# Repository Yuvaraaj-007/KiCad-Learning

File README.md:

# KiCad Learning Projects

This repository contains my PCB design practice projects created while learning KiCad.

## Projects

### 1. LED PCB Design
- My first PCB design project
- Designed a simple LED circuit with a current-limiting resistor
- Learned schematic creation, PCB routing, and DRC verification

### 2. 555 Timer LED Blinking Circuit
- Designed an astable multivibrator using the 555 Timer IC
- Created an LED blinking circuit using resistor-capacitor timing components
- Learned the working of the 555 Timer in astable mode
- Improved PCB layout and routing skills

### 3. Push Button LED Circuit
- Designed a circuit to control an LED using a push button switch
- Learned switch connections and basic input-output circuits
- Practiced schematic design and PCB layout creation

### 4. Transistor LED Circuit
- Designed an LED switching circuit using a transistor
- Learned the basics of transistor operation and switching applications
- Improved understanding of electronic components and PCB design workflow

### 5. Traffic light controller
- PCB schematic design
- PCB layout and routing
- Design Rule Check (DRC)
- KiCad workflow
- Electronic circuit design
- 555 Timer applications
- Switch and transistor circuits
- Traffic light controller design
- Complex PCB routing and component placement

## Skills I Am Learning

- PCB schematic design
- PCB layout and routing
- Design Rule Check (DRC)
- KiCad workflow
- Electronic circuit design
- 555 Timer applications
- Switch and transistor circuits

## Goal

To improve my PCB design skills, strengthen my electronics knowledge, and build real-world embedded and PCB projects step by step.

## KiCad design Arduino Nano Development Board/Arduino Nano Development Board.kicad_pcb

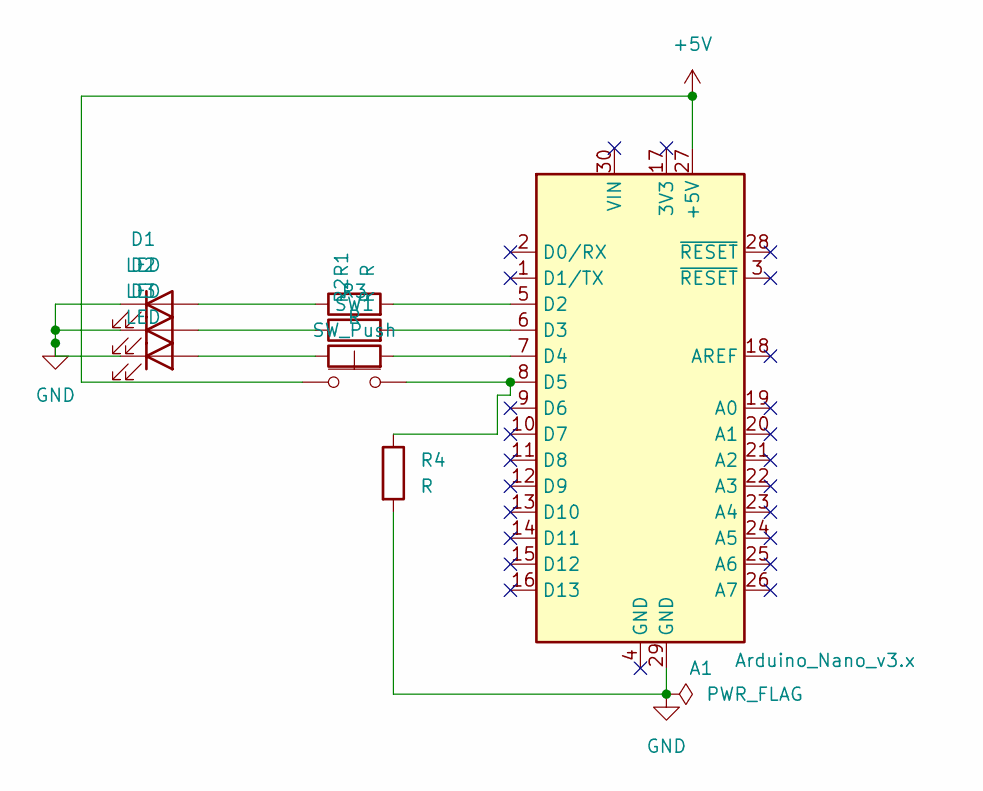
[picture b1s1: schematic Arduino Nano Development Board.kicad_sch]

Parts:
A1: Arduino_Nano_v3.x; Arduino_Nano
D1, D2, D3: LED; LED_D5.0mm
R1, R2, R3, R4: R; R_Axial_DIN0207_L6.3mm_D2.5mm_P7.62mm_Horizontal
SW1: SW_Push; SW_PUSH_6mm

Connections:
+5V: A1.27 (+5V), SW1.1
GND: A1.29 (GND), D1.1 (K), D2.1 (K), D3.1 (K), R4.2
unnamed: A1.5 (D2), R1.2
unnamed: A1.6 (D3), R2.2
unnamed: A1.7 (D4), R3.2
unnamed: A1.8 (D5), R4.1, SW1.2
unnamed: D1.2 (A), R1.1
unnamed: D2.2 (A), R2.1
unnamed: D3.2 (A), R3.1

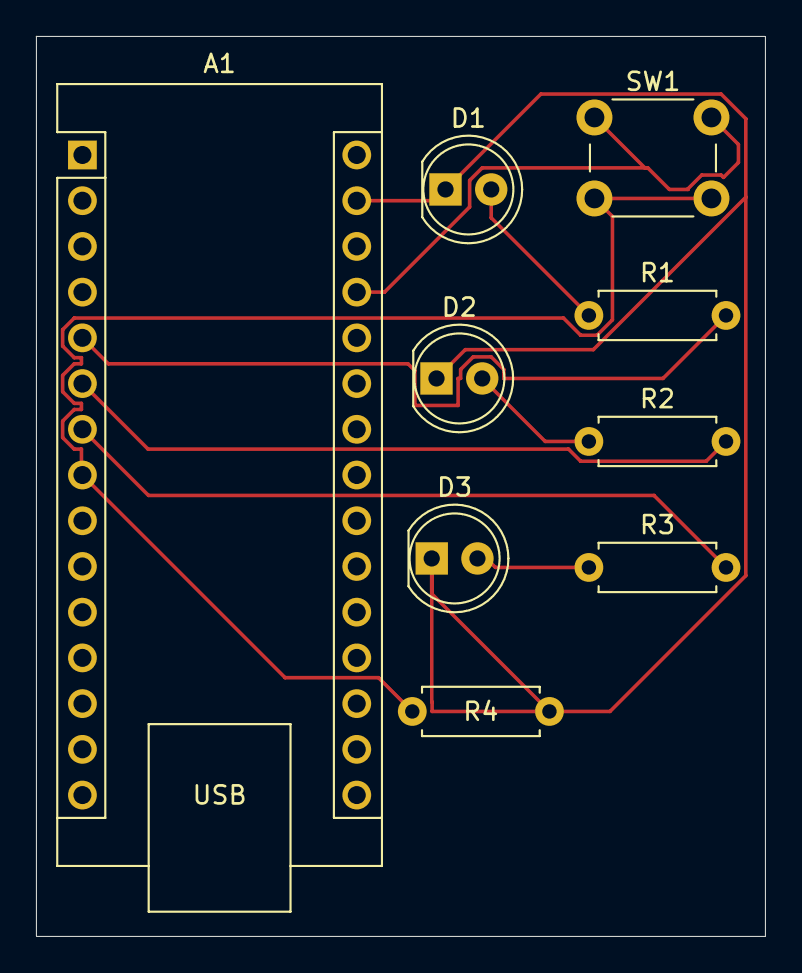
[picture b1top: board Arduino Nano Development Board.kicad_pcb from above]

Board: 2 copper layers, 40.5 x 50.0 mm, 9 parts (0 on the bottom side), 9 nets.

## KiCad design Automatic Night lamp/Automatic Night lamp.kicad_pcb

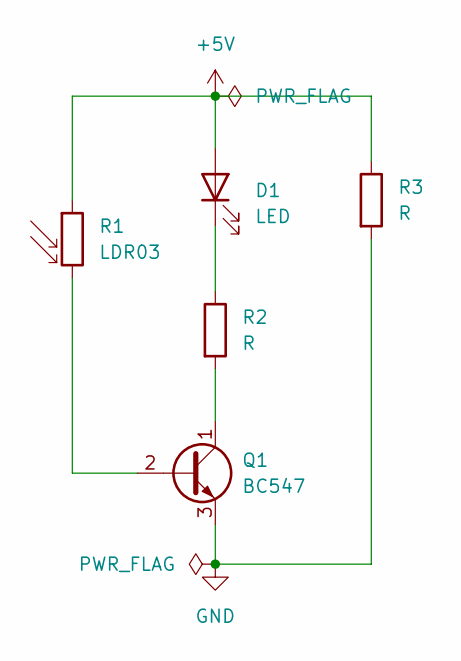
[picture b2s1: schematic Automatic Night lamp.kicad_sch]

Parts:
D1: LED; LED_D5.0mm
Q1: BC547; TO-92_Inline
R1: LDR03; R_LDR_10x8.5mm_P7.6mm_Vertical
R2: R; R_Axial_DIN0207_L6.3mm_D2.5mm_P7.62mm_Horizontal
R3: R; R_Axial_DIN0204_L3.6mm_D1.6mm_P7.62mm_Horizontal

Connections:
+5V: D1.2 (A), R1.1, R3.1
GND: Q1.3 (E), R3.2
unnamed: D1.1 (K), R2.1
unnamed: Q1.2 (B), R1.2
unnamed: Q1.1 (C), R2.2

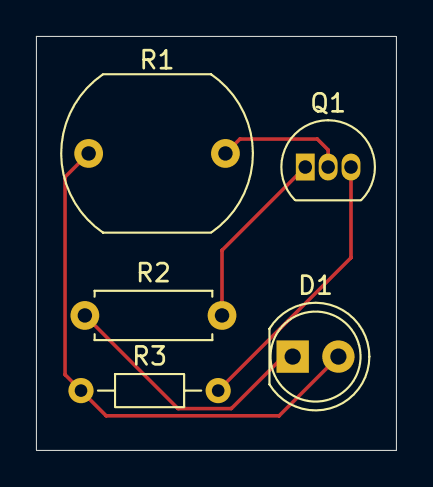
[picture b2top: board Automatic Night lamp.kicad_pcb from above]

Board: 2 copper layers, 20.0 x 23.0 mm, 5 parts (0 on the bottom side), 5 nets.

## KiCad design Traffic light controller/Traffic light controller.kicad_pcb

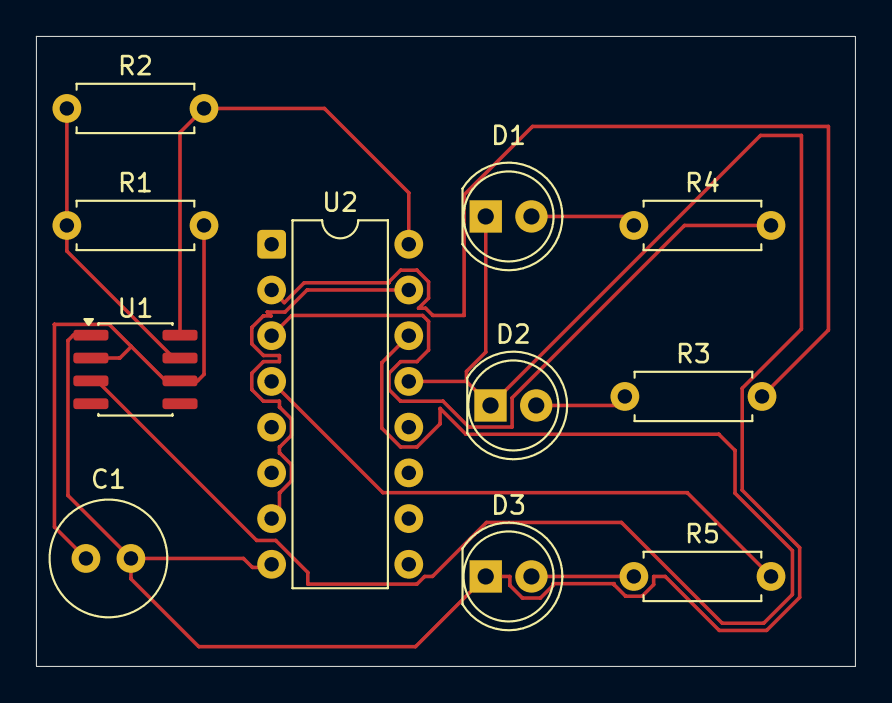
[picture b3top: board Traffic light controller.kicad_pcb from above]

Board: 2 copper layers, 45.5 x 35.0 mm, 11 parts (0 on the bottom side), 11 nets.

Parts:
C1: 10uF; C_Radial_D6.3mm_H5.0mm_P2.50mm
D1: Red; LED_D5.0mm
D2: Yellow; LED_D5.0mm
D3: Green; LED_D5.0mm
R1: 100K; R_Axial_DIN0207_L6.3mm_D2.5mm_P7.62mm_Horizontal
R2: 10K; R_Axial_DIN0207_L6.3mm_D2.5mm_P7.62mm_Horizontal
R3, R4, R5: 330; R_Axial_DIN0207_L6.3mm_D2.5mm_P7.62mm_Horizontal
U1: NE555D; SOIC-8_3.9x4.9mm_P1.27mm
U2: 4017; DIP-16_W7.62mm

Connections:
+5V: R2.2, U1.8 (VCC), U2.16 (VDD)
GND: C1.2, D1.1 (K), D2.1 (K), D3.1 (K_1), U1.1 (GND), U2.8 (VSS), U2.13 (CKEN)
unnamed: D1.2 (A), R4.1
unnamed: D2.2 (A), R3.1
unnamed: R1.1, R2.1, U1.7 (DISCH)
unnamed: U1.3 (OUT), U2.14 (CLK)
unnamed: C1.1, R1.2, U1.2 (TRIG), U1.6 (THRES)
unnamed: R4.2, U2.3 (Q0)
unnamed: R3.2, U2.2 (Q1)
unnamed: R5.2, U2.4 (Q2)
unnamed: U2.7 (Q3), U2.15 (Reset)

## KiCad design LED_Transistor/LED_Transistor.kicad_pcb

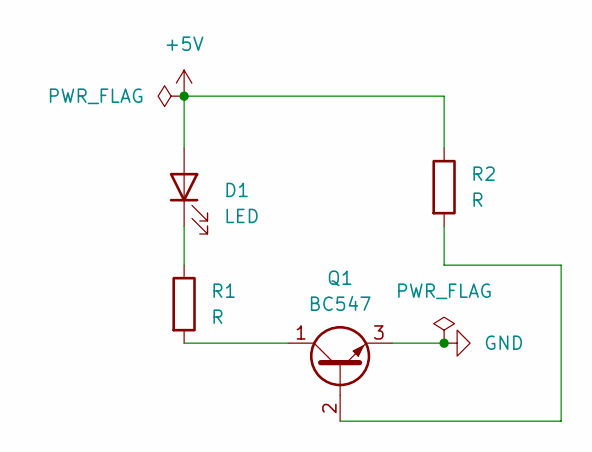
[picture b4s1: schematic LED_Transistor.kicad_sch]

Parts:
D1: LED; LED_D5.0mm
Q1: BC547; TO-92_Inline
R1, R2: R; R_Axial_DIN0207_L6.3mm_D2.5mm_P7.62mm_Horizontal

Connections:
+5V: D1.2 (A), R2.1
GND: Q1.3 (E)
unnamed: D1.1 (K), R1.1
unnamed: Q1.2 (B), R2.2
unnamed: Q1.1 (C), R1.2

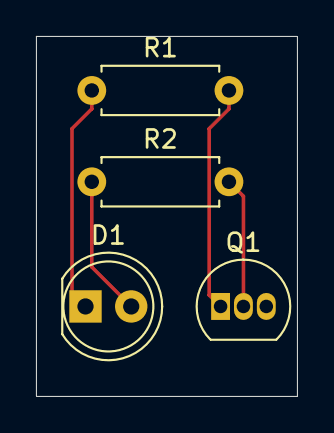
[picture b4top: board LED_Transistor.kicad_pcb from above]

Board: 2 copper layers, 14.5 x 20.0 mm, 4 parts (0 on the bottom side), 4 nets.

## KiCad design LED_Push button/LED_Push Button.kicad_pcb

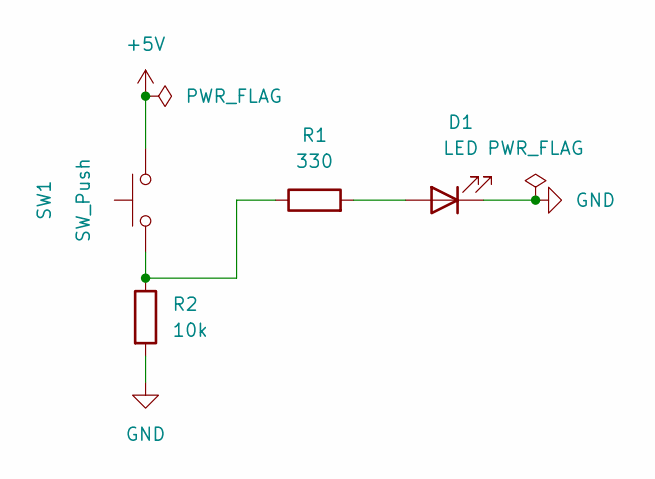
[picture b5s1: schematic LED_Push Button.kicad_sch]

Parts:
D1: LED; LED_D5.0mm
R1: 330; R_Axial_DIN0207_L6.3mm_D2.5mm_P7.62mm_Horizontal
R2: 10k; R_Axial_DIN0207_L6.3mm_D2.5mm_P7.62mm_Horizontal
SW1: SW_Push; SW_PUSH_6mm

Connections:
+5V: SW1.2
GND: D1.1 (K), R2.2
unnamed: D1.2 (A), R1.2
unnamed: R1.1, R2.1, SW1.1

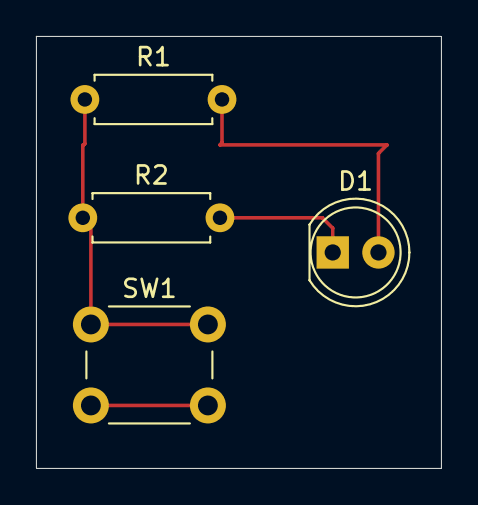
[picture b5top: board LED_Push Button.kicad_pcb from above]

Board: 2 copper layers, 22.5 x 24.0 mm, 4 parts (0 on the bottom side), 3 nets.

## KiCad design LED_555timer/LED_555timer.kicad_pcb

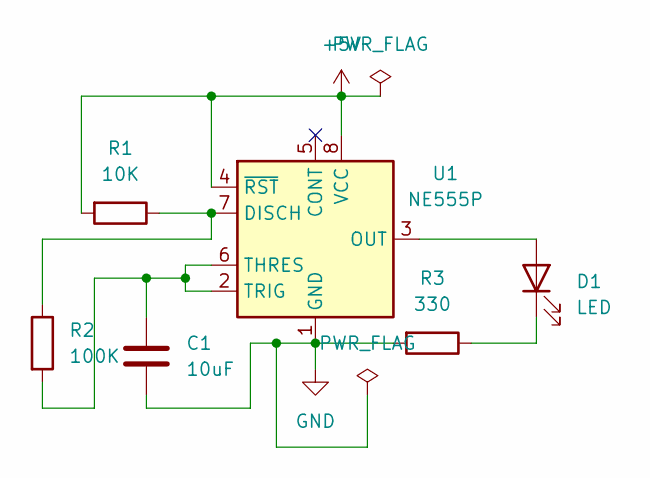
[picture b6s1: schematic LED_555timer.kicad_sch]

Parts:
C1: 10uF; C_Disc_D5.0mm_W2.5mm_P5.00mm
D1: LED; LED_D5.0mm
R1: 10K; R_Axial_DIN0207_L6.3mm_D2.5mm_P7.62mm_Horizontal
R2: 100K; R_Axial_DIN0207_L6.3mm_D2.5mm_P7.62mm_Horizontal
R3: 330; R_Axial_DIN0207_L6.3mm_D2.5mm_P7.62mm_Horizontal
U1: NE555P; DIP-8_W7.62mm

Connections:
+5V: R1.2, U1.4 (~RST), U1.8 (VCC)
GND: C1.2, R3.2, U1.1 (GND)
unnamed: D1.2 (A), U1.3 (OUT)
unnamed: D1.1 (K), R3.1
unnamed: R1.1, R2.1, U1.7 (DISCH)
unnamed: C1.1, R2.2, U1.2 (TRIG), U1.6 (THRES)

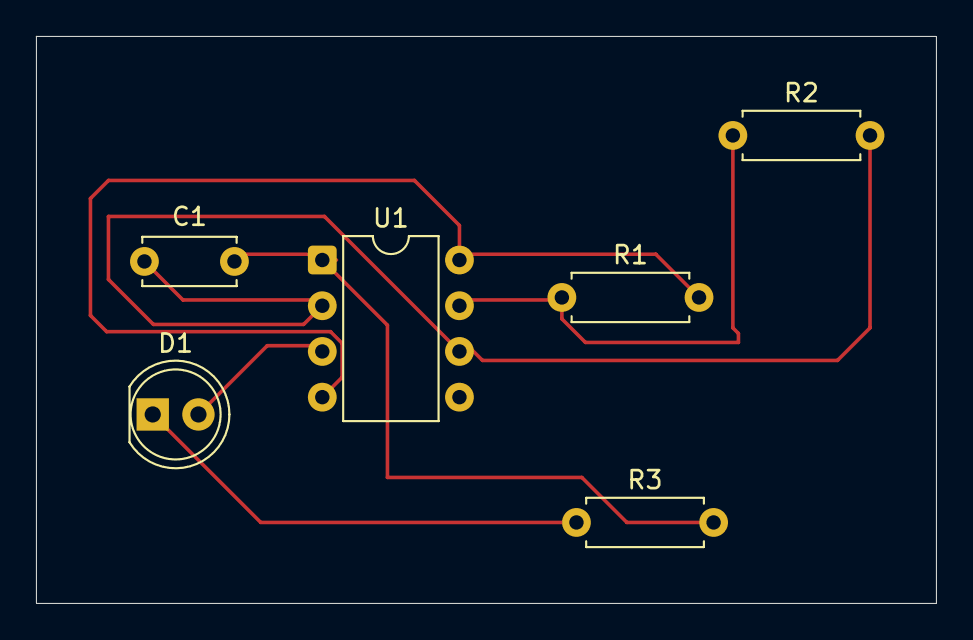
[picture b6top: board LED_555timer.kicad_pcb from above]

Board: 2 copper layers, 50.0 x 31.5 mm, 6 parts (0 on the bottom side), 6 nets.
